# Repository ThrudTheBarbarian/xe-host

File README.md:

# xe-host
T8-based Atari-XE host-interface to XIO

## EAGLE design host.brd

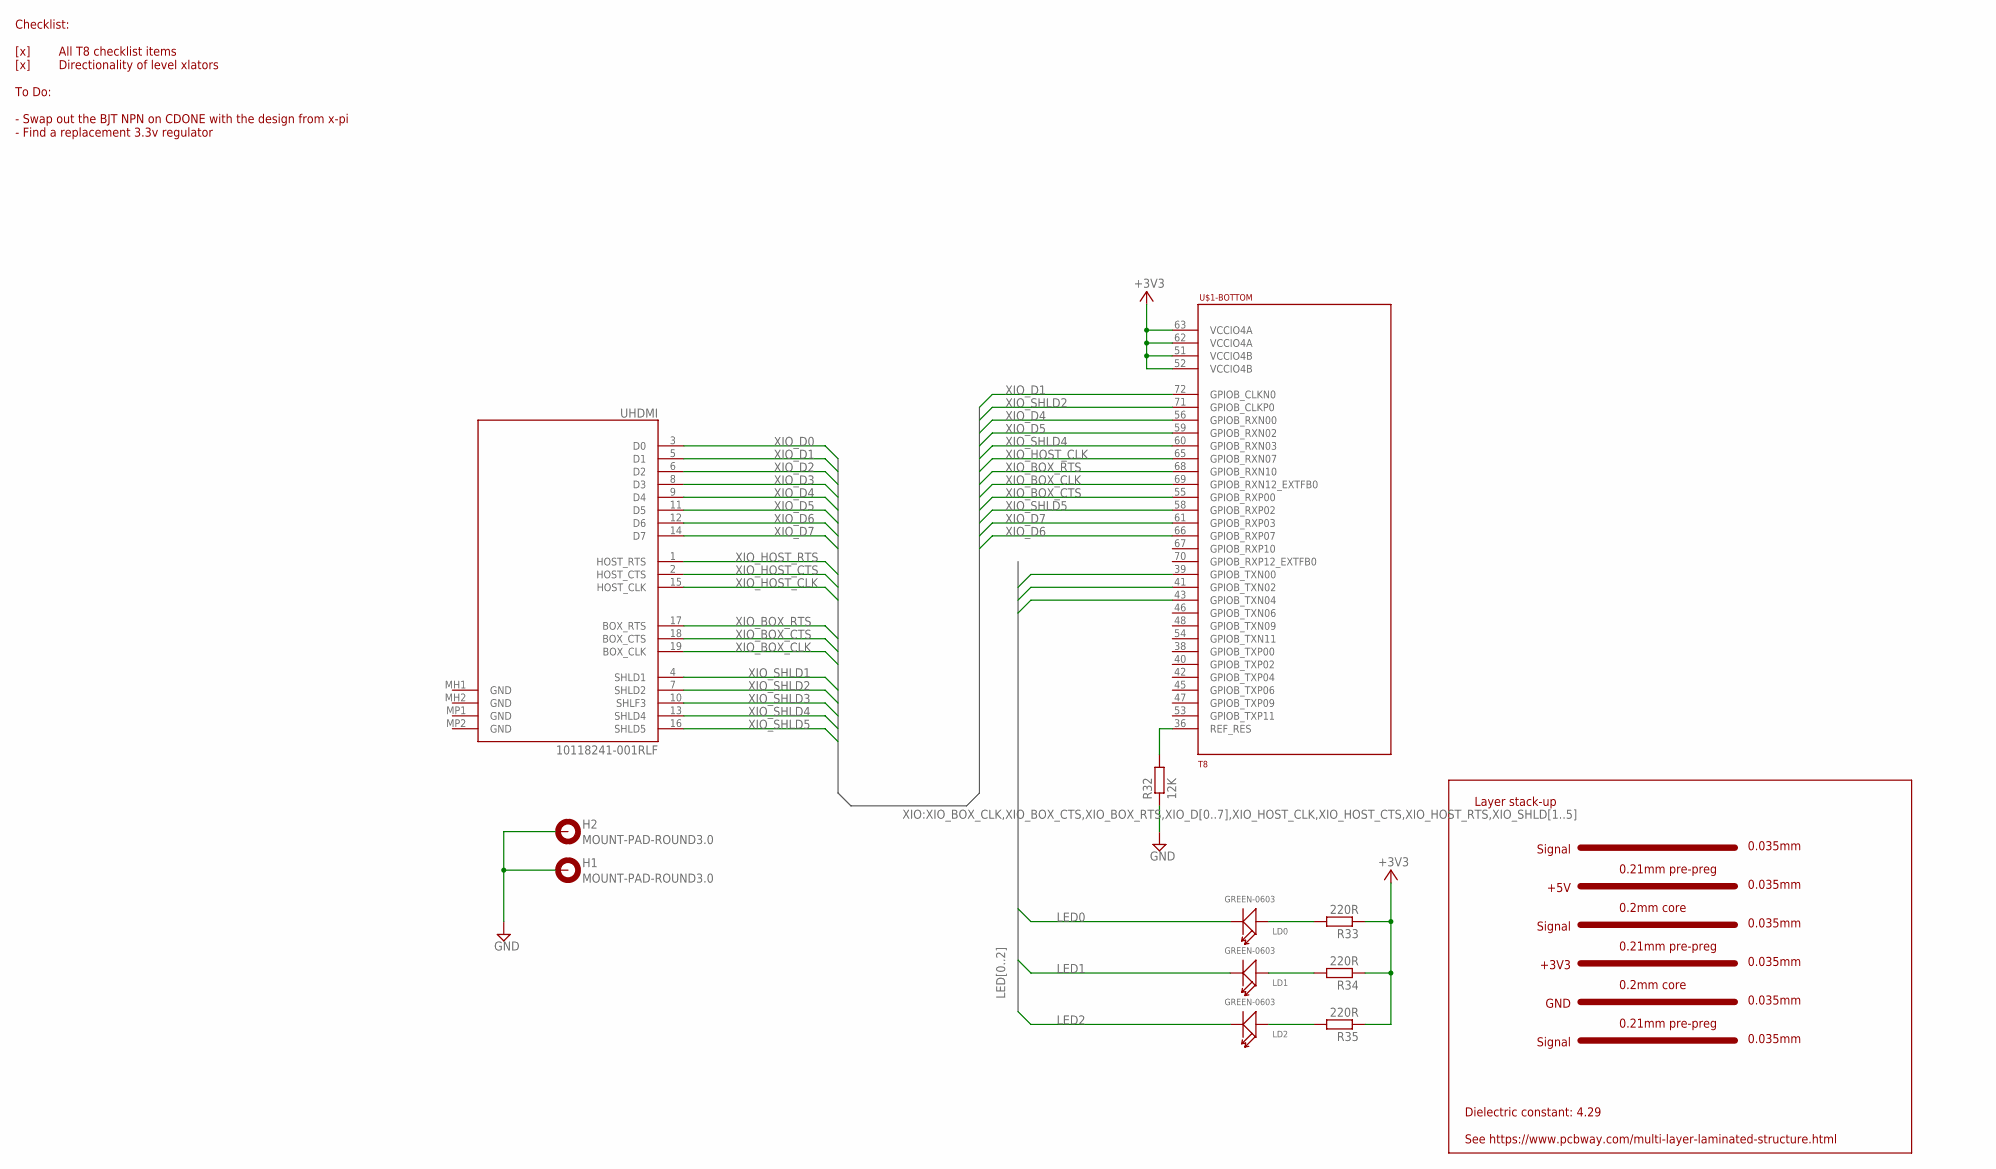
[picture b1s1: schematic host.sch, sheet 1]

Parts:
H1, H2: MOUNT-PAD-ROUND3.0; 3,0-PAD
LD0, LD1, LD2: GREEN-0603; LED-0603
R32: 12K; R0201
R33, R34, R35: 220R; R0201
U$1: T8; TQFP144
UHDMI: 10118241-001RLF; 10118241001RLF

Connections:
+3V3: R33.1, R34.1, R35.1, U$1.51 (VCCIO4B), U$1.52 (VCCIO4B), U$1.62 (VCCIO4A), U$1.63 (VCCIO4A); also elsewhere on the board
GND: H1.B3,0, H2.B3,0, R32.1; also elsewhere on the board
LED0: LD0.-, U$1.39 (GPIOB_TXN00)
LED1: LD1.-, U$1.41 (GPIOB_TXN02)
LED2: LD2.-, U$1.43 (GPIOB_TXN04)
unnamed: R32.2, U$1.36 (REF_RES)
unnamed: LD0.+, R33.2
unnamed: LD1.+, R34.2
unnamed: LD2.+, R35.2
XIO_BOX_CLK: U$1.69 (GPIOB_RXN12_EXTFB0), UHDMI.19 (BOX_CLK); also elsewhere on the board
XIO_BOX_CTS: U$1.55 (GPIOB_RXP00), UHDMI.18 (BOX_CTS); also elsewhere on the board
XIO_BOX_RTS: U$1.68 (GPIOB_RXN10), UHDMI.17 (BOX_RTS); also elsewhere on the board
XIO_D0: UHDMI.3 (D0); also elsewhere on the board
XIO_D1: U$1.72 (GPIOB_CLKN0), UHDMI.5 (D1); also elsewhere on the board
XIO_D2: UHDMI.6 (D2); also elsewhere on the board
XIO_D3: UHDMI.8 (D3); also elsewhere on the board
XIO_D4: U$1.56 (GPIOB_RXN00), UHDMI.9 (D4); also elsewhere on the board
XIO_D5: U$1.59 (GPIOB_RXN02), UHDMI.11 (D5); also elsewhere on the board
XIO_D6: U$1.66 (GPIOB_RXP07), UHDMI.12 (D6); also elsewhere on the board
XIO_D7: U$1.61 (GPIOB_RXP03), UHDMI.14 (D7); also elsewhere on the board
XIO_HOST_CLK: U$1.65 (GPIOB_RXN07), UHDMI.15 (HOST_CLK); also elsewhere on the board
XIO_HOST_CTS: UHDMI.2 (HOST_CTS); also elsewhere on the board
XIO_HOST_RTS: UHDMI.1 (HOST_RTS); also elsewhere on the board
XIO_SHLD1: UHDMI.4 (SHLD1); also elsewhere on the board
XIO_SHLD2: U$1.71 (GPIOB_CLKP0), UHDMI.7 (SHLD2); also elsewhere on the board
XIO_SHLD3: UHDMI.10 (SHLF3); also elsewhere on the board
XIO_SHLD4: U$1.60 (GPIOB_RXN03), UHDMI.13 (SHLD4); also elsewhere on the board
XIO_SHLD5: U$1.58 (GPIOB_RXP02), UHDMI.16 (SHLD5); also elsewhere on the board

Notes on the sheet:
Checklist: [x] All T8 checklist items [x] Directionality of level xlators To Do: - Swap out the BJT NPN on CDONE with the design from x-pi - Find a replacement 3.3v regulator
0.035mm
Layer stack-up
+3V3
Dielectric constant: 4.29 See https://www.pcbway.com/multi-layer-laminated-structure.html
Signal
GND
Signal
+5V
0.21mm pre-preg
0.2mm core

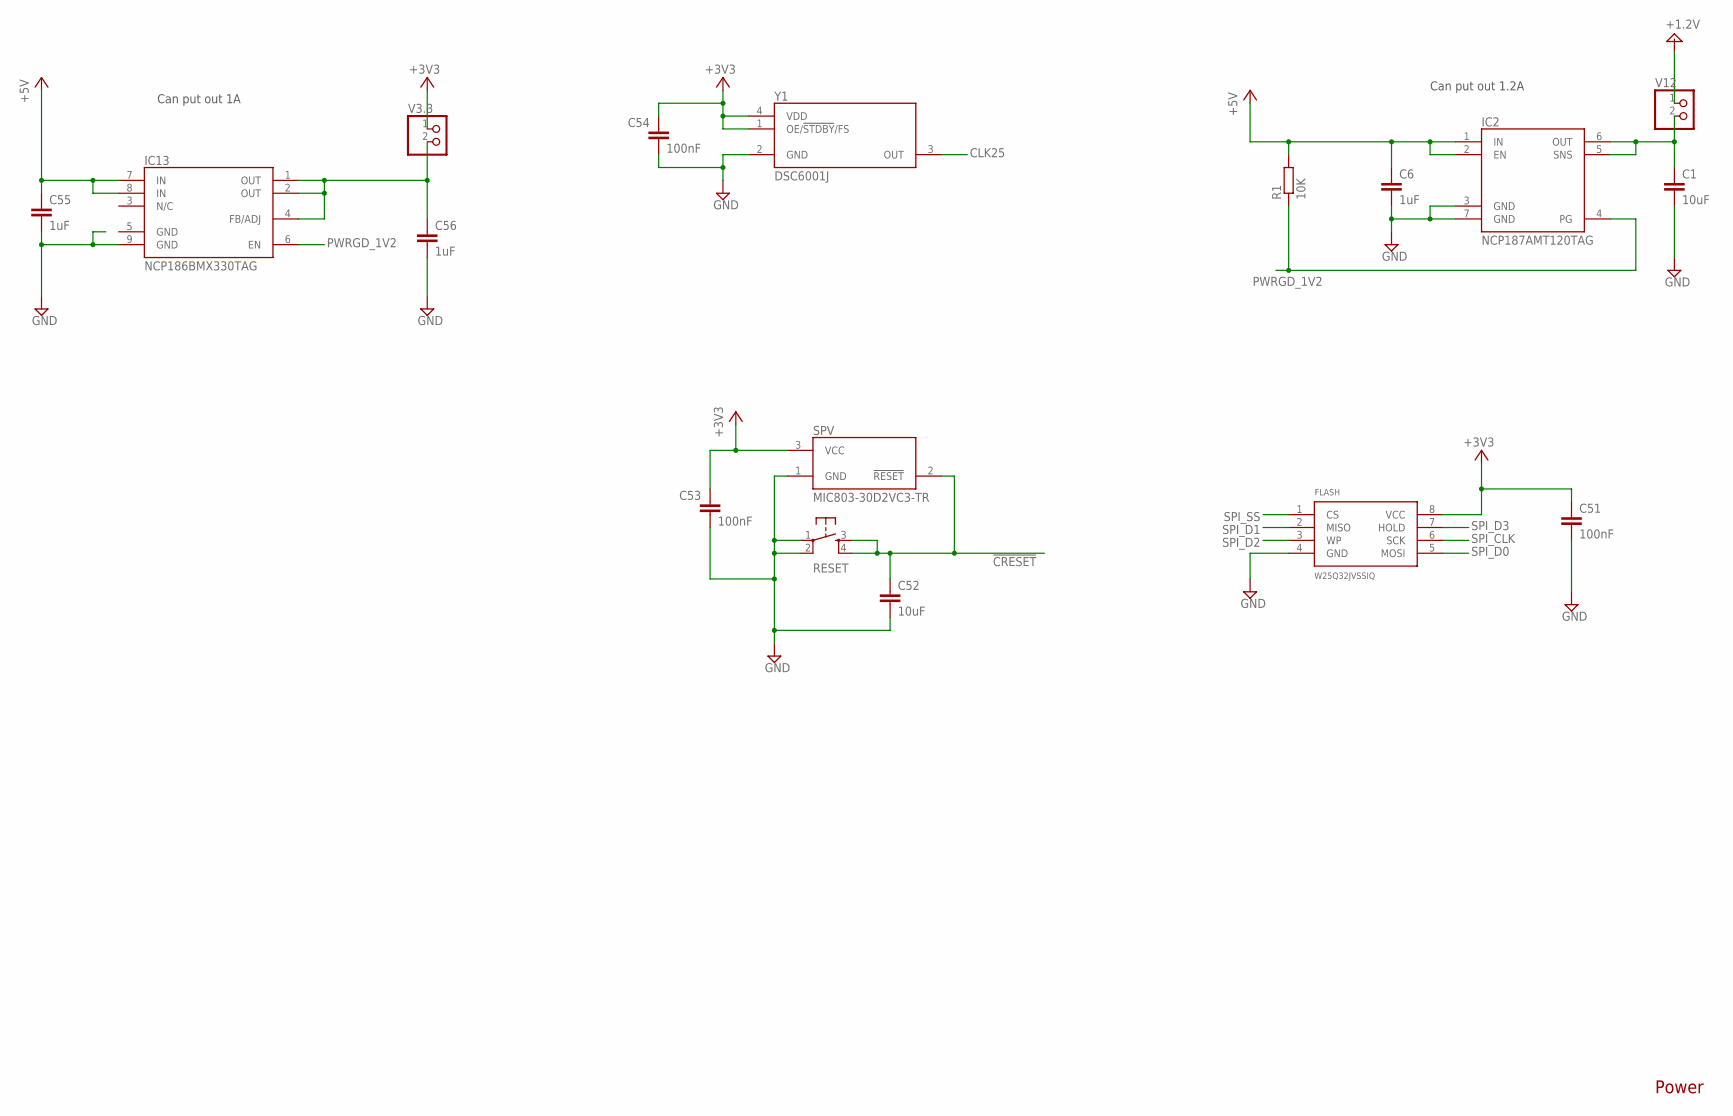
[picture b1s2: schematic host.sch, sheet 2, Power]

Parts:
C1, C52: 10uF; C0402K
C6, C55, C56: 1uF; C0201
C51, C53, C54: 100nF; C0201
FLASH: W25Q32JVSSIQ; SO08
IC2: NCP187AMT120TAG; SON65P200X200X80-7N
IC13: NCP186BMX330TAG; NCP186AMX330TAG
R1: 10K; R0201
RESET: TAC_SWITCHPTH; TACTILE-PTH
SPV: MIC803-30D2VC3-TR; SOT95P237X111-3N
V3.3, V12: PINHD-1X2; 1X02
Y1: DSC6001J; DSC6001JE2B0240000

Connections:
!CRESET!: C52.1, RESET.3, RESET.4, SPV.2 (!RESET!); also elsewhere on the board
+1.2V: V12.1; also elsewhere on the board
+3V3: C51.1, C53.1, C54.1, FLASH.8 (VCC), SPV.3 (VCC), V3.3.1, Y1.1 (OE/!STDBY!/FS), Y1.4 (VDD); also elsewhere on the board
+5V: C6.1, C55.1, IC2.1 (IN), IC2.2 (EN), IC13.7 (IN), IC13.8 (IN), R1.2; also elsewhere on the board
CLK25: Y1.3 (OUT); also elsewhere on the board
GND: C1.2, C6.2, C51.2, C52.2, C53.2, C54.2, C55.2, C56.2, FLASH.4 (GND), IC2.3 (GND), IC2.7 (GND), IC13.9 (GND), RESET.1, RESET.2, SPV.1 (GND), Y1.2 (GND); also elsewhere on the board
unnamed: C1.1, IC2.5 (SNS), IC2.6 (OUT), V12.2
unnamed: C56.1, IC13.1 (OUT), IC13.2 (OUT), IC13.4 (FB/ADJ), V3.3.2
PWRGD_1V2: IC2.4 (PG), IC13.6 (EN), R1.1
SPI_CLK: FLASH.6 (SCK); also elsewhere on the board
SPI_D0: FLASH.5 (MOSI); also elsewhere on the board
SPI_D1: FLASH.2 (MISO); also elsewhere on the board
SPI_D2: FLASH.3 (WP); also elsewhere on the board
SPI_D3: FLASH.7 (HOLD); also elsewhere on the board
SPI_SS: FLASH.1 (CS); also elsewhere on the board

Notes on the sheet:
Power
Can put out 1.2A
Can put out 1A

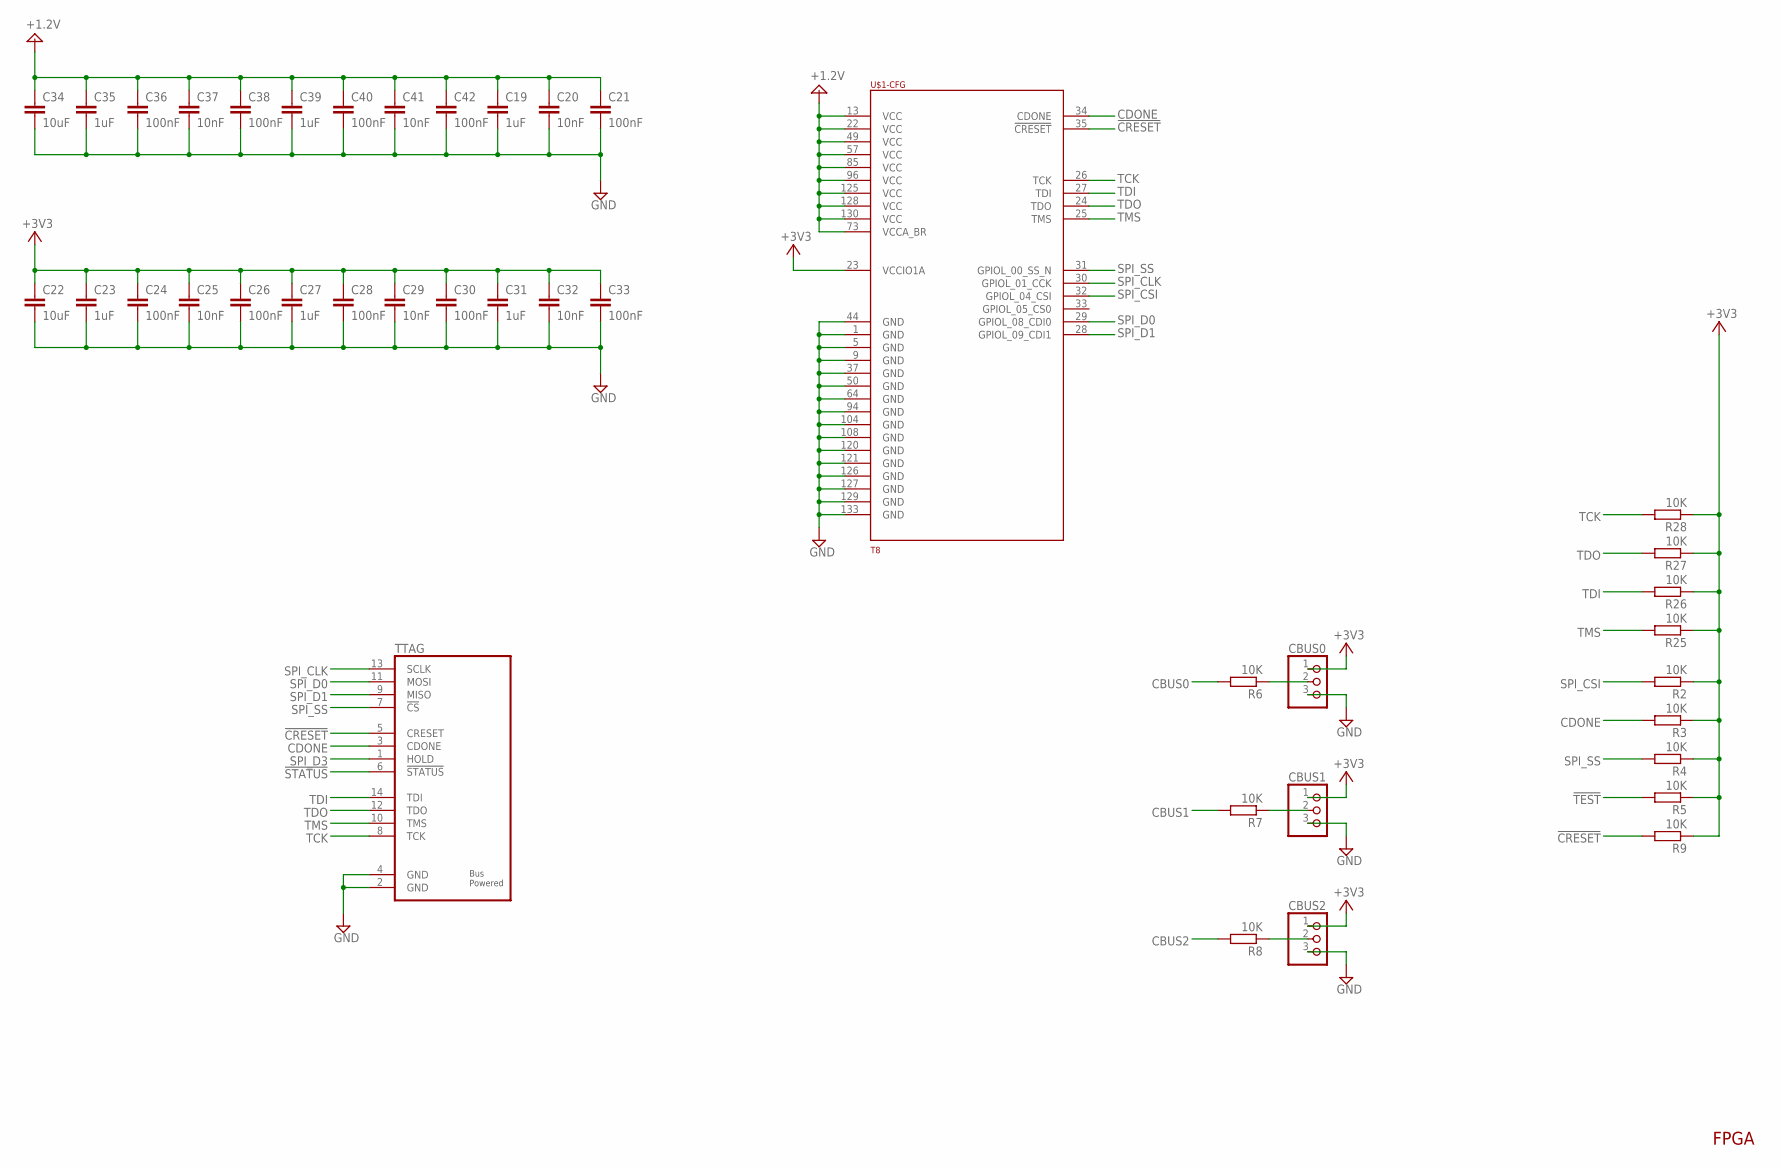
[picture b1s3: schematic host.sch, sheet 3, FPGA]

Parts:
C19, C23, C27, C31, C35, C39: 1uF; C0201
C20, C25, C29, C32, C37, C41: 10nF; C0201
C21, C24, C26, C28, C30, C33, C36, C38, C40, C42: 100nF; C0201
C22, C34: 10uF; C0402K
CBUS0, CBUS1, CBUS2: PINHD-1X3; 1X03
R2, R3, R4, R5, R6, R7, R8, R9, R25, R26, R27, R28: 10K; R0201
TTAG: TTAG_M_2.00; 2X07M
U$1: T8; TQFP144

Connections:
!CRESET!: R9.2, TTAG.5 (CRESET), U$1.35 (!CRESET!); also elsewhere on the board
!STATUS!: TTAG.6 (!STATUS!); also elsewhere on the board
!TEST!: R5.2; also elsewhere on the board
+1.2V: C19.1, C20.1, C21.1, C34.1, C35.1, C36.1, C37.1, C38.1, C39.1, C40.1, C41.1, C42.1, U$1.13 (VCC), U$1.22 (VCC), U$1.49 (VCC), U$1.57 (VCC), U$1.73 (VCCA_BR), U$1.85 (VCC), U$1.96 (VCC), U$1.125 (VCC), U$1.128 (VCC), U$1.130 (VCC); also elsewhere on the board
+3V3: C22.1, C23.1, C24.1, C25.1, C26.1, C27.1, C28.1, C29.1, C30.1, C31.1, C32.1, C33.1, CBUS0.1, CBUS1.1, CBUS2.1, R2.1, R3.1, R4.1, R5.1, R9.1, R25.1, R26.1, R27.1, R28.1, U$1.23 (VCCIO1A); also elsewhere on the board
CBUS0: R6.2; also elsewhere on the board
CBUS1: R7.2; also elsewhere on the board
CBUS2: R8.2; also elsewhere on the board
CDONE: R3.2, TTAG.3 (CDONE), U$1.34 (CDONE); also elsewhere on the board
GND: C19.2, C20.2, C21.2, C22.2, C23.2, C24.2, C25.2, C26.2, C27.2, C28.2, C29.2, C30.2, C31.2, C32.2, C33.2, C34.2, C35.2, C36.2, C37.2, C38.2, C39.2, C40.2, C41.2, C42.2, CBUS0.3, CBUS1.3, CBUS2.3, TTAG.2 (GND), TTAG.4 (GND), U$1.1 (GND), U$1.5 (GND), U$1.9 (GND), U$1.37 (GND), U$1.44 (GND), U$1.50 (GND), U$1.64 (GND), U$1.94 (GND), U$1.104 (GND), U$1.108 (GND), U$1.120 (GND), U$1.121 (GND), U$1.126 (GND), U$1.127 (GND), U$1.129 (GND), U$1.133 (GND); also elsewhere on the board
unnamed: CBUS0.2, R6.1
unnamed: CBUS1.2, R7.1
unnamed: CBUS2.2, R8.1
SPI_CLK: TTAG.13 (SCLK), U$1.30 (GPIOL_01_CCK); also elsewhere on the board
SPI_CSI: R2.2, U$1.32 (GPIOL_04_CSI)
SPI_D0: TTAG.11 (MOSI), U$1.29 (GPIOL_08_CDI0); also elsewhere on the board
SPI_D1: TTAG.9 (MISO), U$1.28 (GPIOL_09_CDI1); also elsewhere on the board
SPI_D3: TTAG.1 (HOLD); also elsewhere on the board
SPI_SS: R4.2, TTAG.7 (!CS!), U$1.31 (GPIOL_00_SS_N); also elsewhere on the board
TCK: R28.2, TTAG.8 (TCK), U$1.26 (TCK)
TDI: R26.2, TTAG.14 (TDI), U$1.27 (TDI)
TDO: R27.2, TTAG.12 (TDO), U$1.24 (TDO)
TMS: R25.2, TTAG.10 (TMS), U$1.25 (TMS)

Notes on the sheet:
FPGA

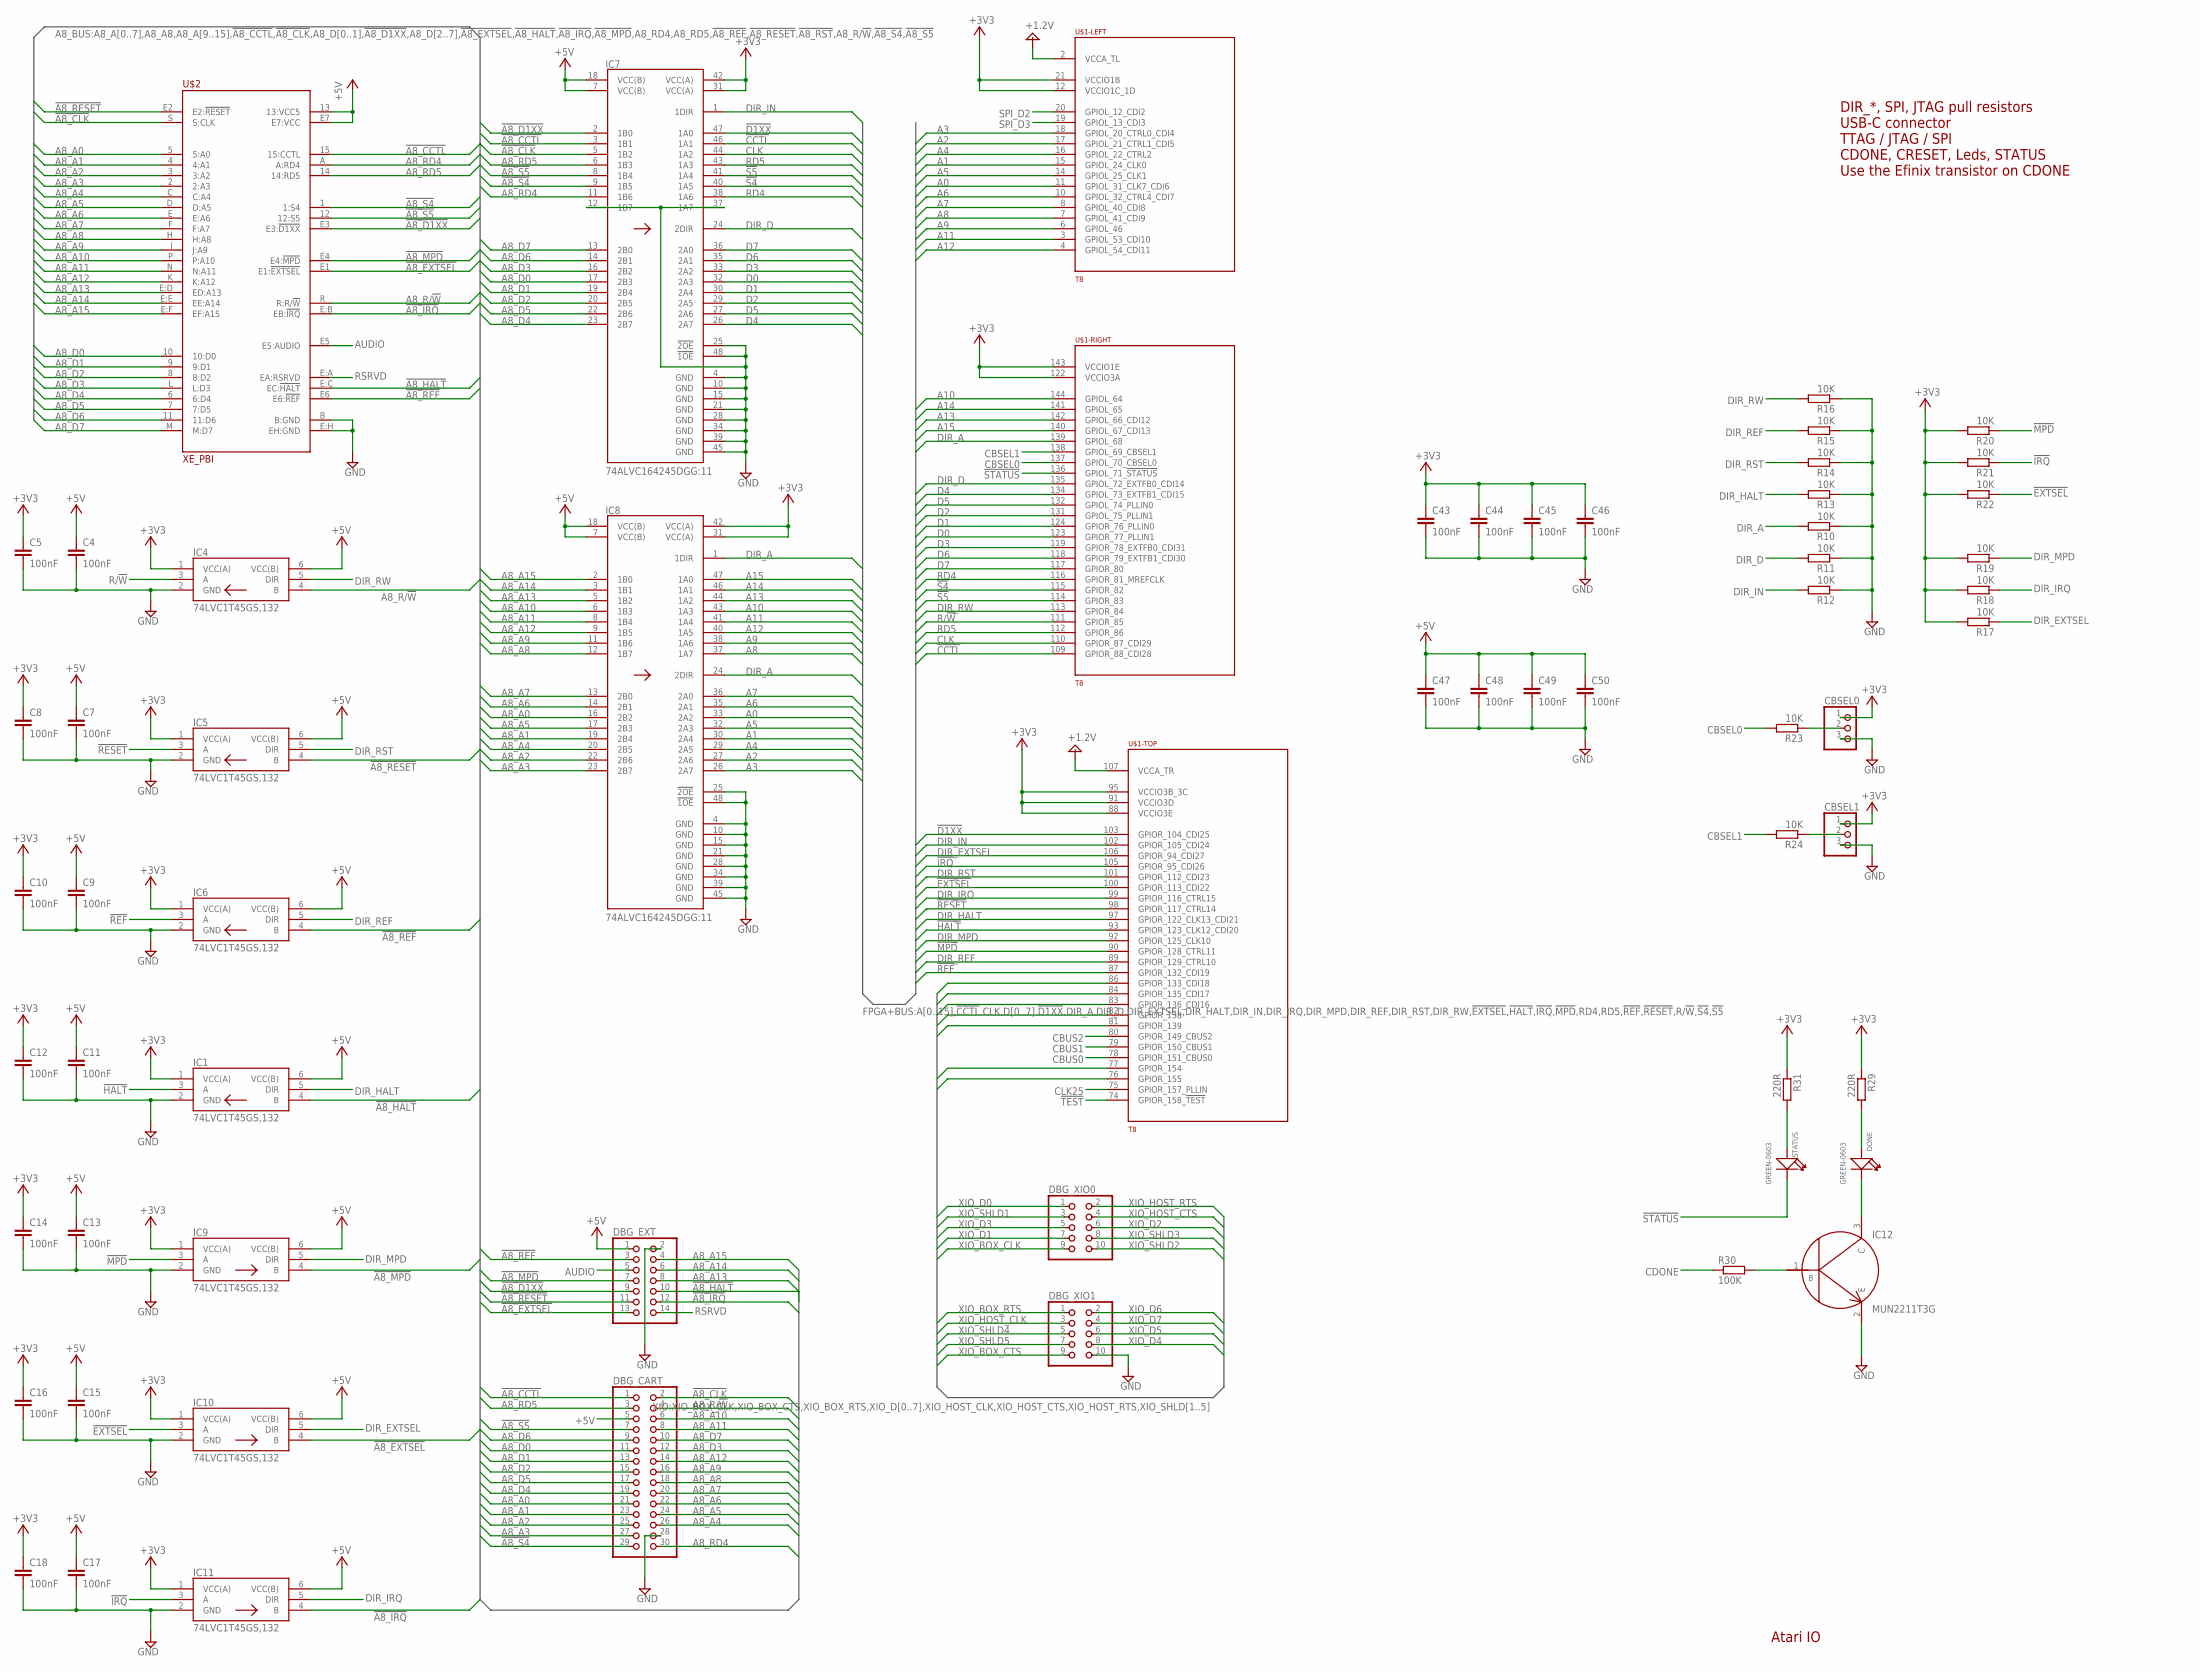
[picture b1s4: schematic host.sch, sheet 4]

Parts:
C4, C5, C7, C8, C9, C10, C11, C12, C13, C14, C15, C16, C17, C18, C43, C44, C45, C46, C47, C48, C49, C50: 100nF; C0201
CBSEL0, CBSEL1: PINHD-1X3; 1X03
DBG_CART: PINHD-2X15_2.54; 2X15
DBG_EXT: PINHD-2X07_2.54; 2X07
DBG_XIO0, DBG_XIO1: PINHD-2X5; 2X05
DONE: GREEN-0603; LED-0603
IC1, IC4, IC5, IC6, IC9, IC10, IC11: 74LVC1T45GS,132; 74LVC1G3157GS132
IC7, IC8: 74ALVC164245DGG:11; SOP50P810X120-48N
IC12: MUN2211T3G; SOTFL50P160X78-3N
R10, R11, R12, R13, R14, R15, R16, R17, R18, R19, R20, R21, R22, R23, R24: 10K; R0201
R29, R31: 220R; R0201
R30: 100K; R0201
STATUS: GREEN-0603; LED-0603
U$1: T8; TQFP144
U$2: XE_PBI

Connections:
!A8_CCTL!: DBG_CART.1, IC7.3 (1B1), U$2.15 (15:CCTL)
!A8_CLK!: DBG_CART.2, IC7.5 (1B2), U$2.S (S:CLK)
!A8_D1XX!: DBG_EXT.9, IC7.2 (1B0), U$2.E3 (E3:!D1XX!)
!A8_EXTSEL!: DBG_EXT.13, IC10.4 (B), U$2.E1 (E1:!EXTSEL!)
!A8_HALT!: DBG_EXT.10, IC1.4 (B), U$2.E:C (EC:!HALT!)
!A8_IRQ!: DBG_EXT.12, IC11.4 (B), U$2.E:B (EB:!IRQ!)
!A8_MPD!: DBG_EXT.7, IC9.4 (B), U$2.E4 (E4:!MPD!)
!A8_REF!: DBG_EXT.3, IC6.4 (B), U$2.E6 (E6:!REF!)
!A8_RESET!: DBG_EXT.11, IC5.4 (B), U$2.E2 (E2:!RESET!)
!A8_S4!: DBG_CART.29, IC7.9 (1B5), U$2.1 (1:S4)
!A8_S5!: DBG_CART.7, IC7.8 (1B4), U$2.12 (12:S5)
!CCTL!: IC7.46 (1A1), U$1.109 (GPIOR_88_CDI28)
!D1XX!: IC7.47 (1A0), U$1.103 (GPIOR_104_CDI25)
!EXTSEL!: IC10.3 (A), R22.1, U$1.100 (GPIOR_113_CDI22)
!HALT!: IC1.3 (A), U$1.93 (GPIOR_123_CLK12_CDI20)
!IRQ!: IC11.3 (A), R21.1, U$1.105 (GPIOR_95_CDI26)
!MPD!: IC9.3 (A), R20.1, U$1.90 (GPIOR_128_CTRL11)
!REF!: IC6.3 (A), U$1.87 (GPIOR_132_CDI19)
!RESET!: IC5.3 (A), U$1.98 (GPIOR_117_CTRL14)
!S4!: IC7.40 (1A5), U$1.115 (GPIOR_82)
!S5!: IC7.41 (1A4), U$1.114 (GPIOR_83)
!STATUS!: STATUS.-, U$1.136 (GPIOL_71_!STATUS!); also elsewhere on the board
!TEST!: U$1.74 (GPIOR_158_!TEST!); also elsewhere on the board
+1.2V: U$1.2 (VCCA_TL), U$1.107 (VCCA_TR); also elsewhere on the board
+3V3: C5.1, C8.1, C10.1, C12.1, C14.1, C16.1, C18.1, C43.1, C44.1, C45.1, C46.1, CBSEL0.1, CBSEL1.1, IC1.1 (VCC(A)), IC4.1 (VCC(A)), IC5.1 (VCC(A)), IC6.1 (VCC(A)), IC7.31 (VCC(A)), IC7.42 (VCC(A)), IC8.31 (VCC(A)), IC8.42 (VCC(A)), IC9.1 (VCC(A)), IC10.1 (VCC(A)), IC11.1 (VCC(A)), R17.2, R18.2, R19.2, R20.2, R21.2, R22.2, R29.1, R31.1, U$1.12 (VCCIO1C_1D), U$1.21 (VCCIO1B), U$1.88 (VCCIO3E), U$1.91 (VCCIO3D), U$1.95 (VCCIO3B_3C), U$1.122 (VCCIO3A), U$1.143 (VCCIO1E); also elsewhere on the board
+5V: C4.1, C7.1, C9.1, C11.1, C13.1, C15.1, C17.1, C47.1, C48.1, C49.1, C50.1, DBG_CART.5, DBG_EXT.1, IC1.6 (VCC(B)), IC4.6 (VCC(B)), IC5.6 (VCC(B)), IC6.6 (VCC(B)), IC7.7 (VCC(B)), IC7.18 (VCC(B)), IC8.7 (VCC(B)), IC8.18 (VCC(B)), IC9.6 (VCC(B)), IC10.6 (VCC(B)), IC11.6 (VCC(B)), U$2.13 (13:VCC5), U$2.E7 (E7:VCC); also elsewhere on the board
A0: IC8.33 (2A2), U$1.11 (GPIOL_31_CLK7_CDI6)
A1: IC8.30 (2A4), U$1.15 (GPIOL_24_CLK0)
A2: IC8.27 (2A6), U$1.17 (GPIOL_21_CTRL1_CDI5)
A3: IC8.26 (2A7), U$1.18 (GPIOL_20_CTRL0_CDI4)
A4: IC8.29 (2A5), U$1.16 (GPIOL_22_CTRL2)
A5: IC8.32 (2A3), U$1.14 (GPIOL_25_CLK1)
A6: IC8.35 (2A1), U$1.10 (GPIOL_32_CTRL4_CDI7)
A7: IC8.36 (2A0), U$1.8 (GPIOL_40_CDI8)
A8: IC8.37 (1A7), U$1.7 (GPIOL_41_CDI9)
A8_A0: DBG_CART.21, IC8.16 (2B2), U$2.5 (5:A0)
A8_A1: DBG_CART.23, IC8.19 (2B4), U$2.4 (4:A1)
A8_A2: DBG_CART.25, IC8.22 (2B6), U$2.3 (3:A2)
A8_A3: DBG_CART.27, IC8.23 (2B7), U$2.2 (2:A3)
A8_A4: DBG_CART.26, IC8.20 (2B5), U$2.C (C:A4)
A8_A5: DBG_CART.24, IC8.17 (2B3), U$2.D (D:A5)
A8_A6: DBG_CART.22, IC8.14 (2B1), U$2.E (E:A6)
A8_A7: DBG_CART.20, IC8.13 (2B0), U$2.F (F:A7)
A8_A8: DBG_CART.18, IC8.12 (1B7), U$2.H (H:A8)
A8_A9: DBG_CART.16, IC8.11 (1B6), U$2.J (J:A9)
A8_A10: DBG_CART.6, IC8.6 (1B3), U$2.P (P:A10)
A8_A11: DBG_CART.8, IC8.8 (1B4), U$2.N (N:A11)
A8_A12: DBG_CART.14, IC8.9 (1B5), U$2.K (K:A12)
A8_A13: DBG_EXT.8, IC8.5 (1B2), U$2.E:D (ED:A13)
A8_A14: DBG_EXT.6, IC8.3 (1B1), U$2.E:E (EE:A14)
A8_A15: DBG_EXT.4, IC8.2 (1B0), U$2.E:F (EF:A15)
A8_D0: DBG_CART.11, IC7.17 (2B3), U$2.10 (10:D0)
A8_D1: DBG_CART.13, IC7.19 (2B4), U$2.9 (9:D1)
A8_D2: DBG_CART.15, IC7.20 (2B5), U$2.8 (8:D2)
A8_D3: DBG_CART.12, IC7.16 (2B2), U$2.L (L:D3)
A8_D4: DBG_CART.19, IC7.23 (2B7), U$2.6 (6:D4)
A8_D5: DBG_CART.17, IC7.22 (2B6), U$2.7 (7:D5)
A8_D6: DBG_CART.9, IC7.14 (2B1), U$2.11 (11:D6)
A8_D7: DBG_CART.10, IC7.13 (2B0), U$2.M (M:D7)
A8_R/!W!: DBG_CART.4, IC4.4 (B), U$2.R (R:R/!W!)
A8_RD4: DBG_CART.30, IC7.11 (1B6), U$2.A (A:RD4)
A8_RD5: DBG_CART.3, IC7.6 (1B3), U$2.14 (14:RD5)
A9: IC8.38 (1A6), U$1.6 (GPIOL_46)
A10: IC8.43 (1A3), U$1.144 (GPIOL_64)
A11: IC8.41 (1A4), U$1.3 (GPIOL_53_CDI10)
A12: IC8.40 (1A5), U$1.4 (GPIOL_54_CDI11)
A13: IC8.44 (1A2), U$1.142 (GPIOL_66_CDI12)
A14: IC8.46 (1A1), U$1.141 (GPIOL_65)
A15: IC8.47 (1A0), U$1.140 (GPIOL_67_CDI13)
AUDIO: DBG_EXT.5, U$2.E5 (E5:AUDIO)
CBSEL0: R23.2, U$1.137 (GPIOL_70_CBSEL0)
CBSEL1: R24.2, U$1.138 (GPIOL_69_CBSEL1)
CBUS0: U$1.78 (GPIOR_151_CBUS0); also elsewhere on the board
CBUS1: U$1.79 (GPIOR_150_CBUS1); also elsewhere on the board
CBUS2: U$1.80 (GPIOR_149_CBUS2); also elsewhere on the board
CDONE: R30.1; also elsewhere on the board
CLK: IC7.44 (1A2), U$1.110 (GPIOR_87_CDI29)
CLK25: U$1.75 (GPIOR_157_PLLIN); also elsewhere on the board
D0: IC7.32 (2A3), U$1.123 (GPIOR_77_PLLIN1)
D1: IC7.30 (2A4), U$1.124 (GPIOR_76_PLLIN0)
D2: IC7.29 (2A5), U$1.131 (GPIOL_75_PLLIN1)
D3: IC7.33 (2A2), U$1.119 (GPIOR_78_EXTFB0_CDI31)
D4: IC7.26 (2A7), U$1.134 (GPIOL_73_EXTFB1_CDI15)
D5: IC7.27 (2A6), U$1.132 (GPIOL_74_PLLIN0)
D6: IC7.35 (2A1), U$1.118 (GPIOR_79_EXTFB1_CDI30)
D7: IC7.36 (2A0), U$1.117 (GPIOR_80)
DIR_A: IC8.1 (1DIR), IC8.24 (2DIR), R10.2, U$1.139 (GPIOL_68)
DIR_D: IC7.24 (2DIR), R11.2, U$1.135 (GPIOL_72_EXTFB0_CDI14)
DIR_EXTSEL: IC10.5 (DIR), R17.1, U$1.106 (GPIOR_94_CDI27)
DIR_HALT: IC1.5 (DIR), R13.2, U$1.97 (GPIOR_122_CLK13_CDI21)
DIR_IN: IC7.1 (1DIR), R12.2, U$1.102 (GPIOR_105_CDI24)
DIR_IRQ: IC11.5 (DIR), R18.1, U$1.99 (GPIOR_116_CTRL15)
DIR_MPD: IC9.5 (DIR), R19.1, U$1.92 (GPIOR_125_CLK10)
DIR_REF: IC6.5 (DIR), R15.2, U$1.89 (GPIOR_129_CTRL10)
DIR_RST: IC5.5 (DIR), R14.2, U$1.101 (GPIOR_112_CDI23)
DIR_RW: IC4.5 (DIR), R16.2, U$1.113 (GPIOR_84)
GND: C4.2, C5.2, C7.2, C8.2, C9.2, C10.2, C11.2, C12.2, C13.2, C14.2, C15.2, C16.2, C17.2, C18.2, C43.2, C44.2, C45.2, C46.2, C47.2, C48.2, C49.2, C50.2, CBSEL0.3, CBSEL1.3, DBG_CART.28, DBG_EXT.2, DBG_XIO1.10, IC1.2 (GND), IC4.2 (GND), IC5.2 (GND), IC6.2 (GND), IC7.4 (GND), IC7.10 (GND), IC7.12 (1B7), IC7.15 (GND), IC7.21 (GND), IC7.25 (!2OE), IC7.28 (GND), IC7.34 (GND), IC7.37 (1A7), IC7.39 (GND), IC7.45 (GND), IC7.48 (!1OE), IC8.4 (GND), IC8.10 (GND), IC8.15 (GND), IC8.21 (GND), IC8.25 (!2OE), IC8.28 (GND), IC8.34 (GND), IC8.39 (GND), IC8.45 (GND), IC8.48 (!1OE), IC9.2 (GND), IC10.2 (GND), IC11.2 (GND), IC12.2 (E), R10.1, R11.1, R12.1, R13.1, R14.1, R15.1, R16.1, U$2.B (B:GND), U$2.E:H (EH:GND); also elsewhere on the board
unnamed: CBSEL0.2, R23.1
unnamed: CBSEL1.2, R24.1
unnamed: IC12.1 (B), R30.2
unnamed: DONE.-, IC12.3 (C)
unnamed: DONE.+, R29.2
unnamed: R31.2, STATUS.+
R/!W!: IC4.3 (A), U$1.111 (GPIOR_85)
RD4: IC7.38 (1A6), U$1.116 (GPIOR_81_MREFCLK)
RD5: IC7.43 (1A3), U$1.112 (GPIOR_86)
RSRVD: DBG_EXT.14, U$2.E:A (EA:RSRVD)
SPI_D2: U$1.20 (GPIOL_12_CDI2); also elsewhere on the board
SPI_D3: U$1.19 (GPIOL_13_CDI3); also elsewhere on the board
XIO_BOX_CLK: DBG_XIO0.9; also elsewhere on the board
XIO_BOX_CTS: DBG_XIO1.9; also elsewhere on the board
XIO_BOX_RTS: DBG_XIO1.1; also elsewhere on the board
XIO_D0: DBG_XIO0.1, U$1.84 (GPIOR_135_CDI17); also elsewhere on the board
XIO_D1: DBG_XIO0.7; also elsewhere on the board
XIO_D2: DBG_XIO0.6, U$1.81 (GPIOR_139); also elsewhere on the board
XIO_D3: DBG_XIO0.5, U$1.77 (GPIOR_154); also elsewhere on the board
XIO_D4: DBG_XIO1.8; also elsewhere on the board
XIO_D5: DBG_XIO1.6; also elsewhere on the board
XIO_D6: DBG_XIO1.2; also elsewhere on the board
XIO_D7: DBG_XIO1.4; also elsewhere on the board
XIO_HOST_CLK: DBG_XIO1.3; also elsewhere on the board
XIO_HOST_CTS: DBG_XIO0.4, U$1.83 (GPIOR_136_CDI16); also elsewhere on the board
XIO_HOST_RTS: DBG_XIO0.2, U$1.86 (GPIOR_133_CDI18); also elsewhere on the board
XIO_SHLD1: DBG_XIO0.3, U$1.82 (GPIOR_138); also elsewhere on the board
XIO_SHLD2: DBG_XIO0.10; also elsewhere on the board
XIO_SHLD3: DBG_XIO0.8, U$1.76 (GPIOR_155); also elsewhere on the board
XIO_SHLD4: DBG_XIO1.5; also elsewhere on the board
XIO_SHLD5: DBG_XIO1.7; also elsewhere on the board

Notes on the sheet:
Atari IO
DIR_*, SPI, JTAG pull resistors USB-C connector TTAG / JTAG / SPI CDONE, CRESET, Leds, STATUS Use the Efinix transistor on CDONE

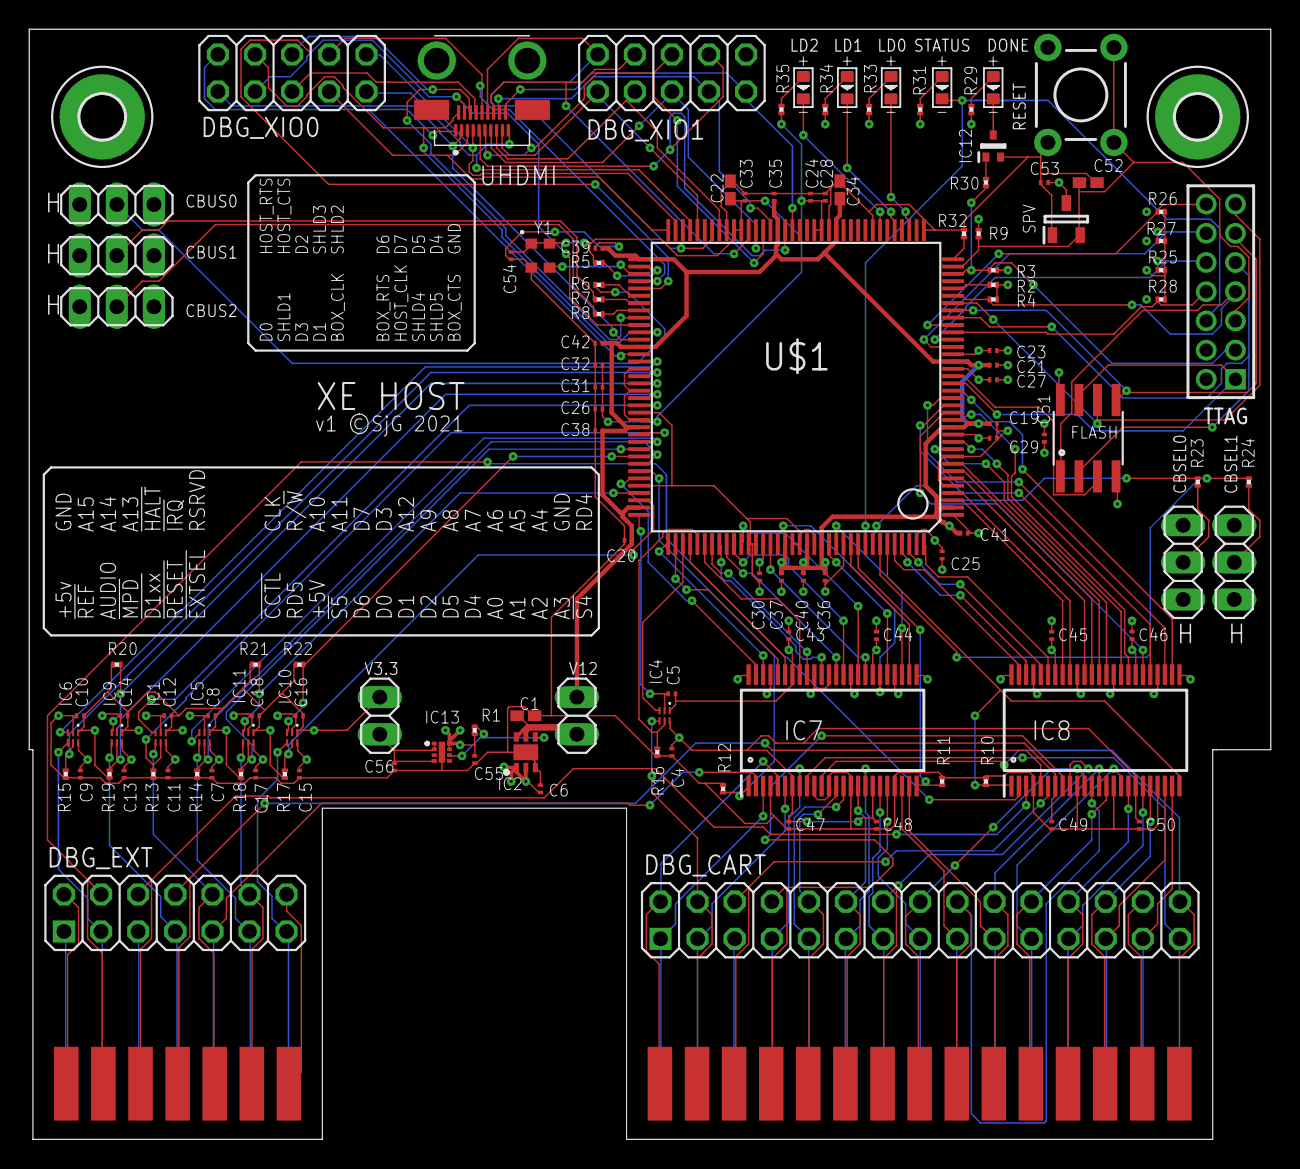
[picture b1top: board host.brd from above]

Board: 4 copper layers, 85.0 x 76.0 mm, 127 parts (0 on the bottom side), 151 nets.

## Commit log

2021-09-22 initial import
2021-09-22 Add the level changes (mostly, still need decoupling and connection to FPGA)
2021-09-23 Move to 6-layer board for supply cleanliness
2021-09-23 Hook up the level-translators to the FPGA
2021-09-23 Add FPGA decoupling caps
2021-09-23 Add level-translation decoupling caps
2021-09-24 Working through the design-guide
2021-09-24 Move to micro-HDMI for the interconnect cable
2021-09-25 Add in the debug headers
2021-09-25 Running through the checklist
2021-09-25 Add the micro-HDMI interface
2021-09-26 Autorouted
2021-09-27 sync
2021-09-28 Change to available parts
2021-09-28 As uploaded to nextpcb
2021-09-28 Using only 4 layers
2021-09-29 Add some costings in

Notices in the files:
host.brd:
v1 ©SjG 2021
parts and their libraries:
SparkFun: Licensing: CC v3.0 Share-Alike You are welcome to use this library for commercial purposes.
